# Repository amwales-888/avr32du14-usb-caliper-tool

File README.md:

# avr32du14-usb-caliper-tool
Tools that connects to caliper port to provide USB connectivity.

Q. What does it do?</BR>
A. You plug it in to your caliper, measure something and press the button, the value is sent to the USB Host as though it was typed by a keyboard.</BR>

The initial PCB run is being made base on the current kicad/avr32du14/production/avr32du14.zip
The enclosure was 3d printed in PLA using a 0.2mm nozzle. It is unlikely to print with 0.4 nozzles without additional work as the wall thicknesses are so thin.
Firmware has not be written but should be fairly trivial as it is simply a USB HID keyboard interface along with some additional code to obtain the values from the caliper.
This is very much a work in progress but I needed somewhere to stash the project.

<table>
  <tr>
    <td> </td>
    <td> </td>
  </tr>
  <tr>
    <td> </td>
    <td> </td>
  </tr>
  <tr>
    <td> </td>
    <td> </td>
  </tr>
  <tr>
    <td> </td>
  </tr>
</table>

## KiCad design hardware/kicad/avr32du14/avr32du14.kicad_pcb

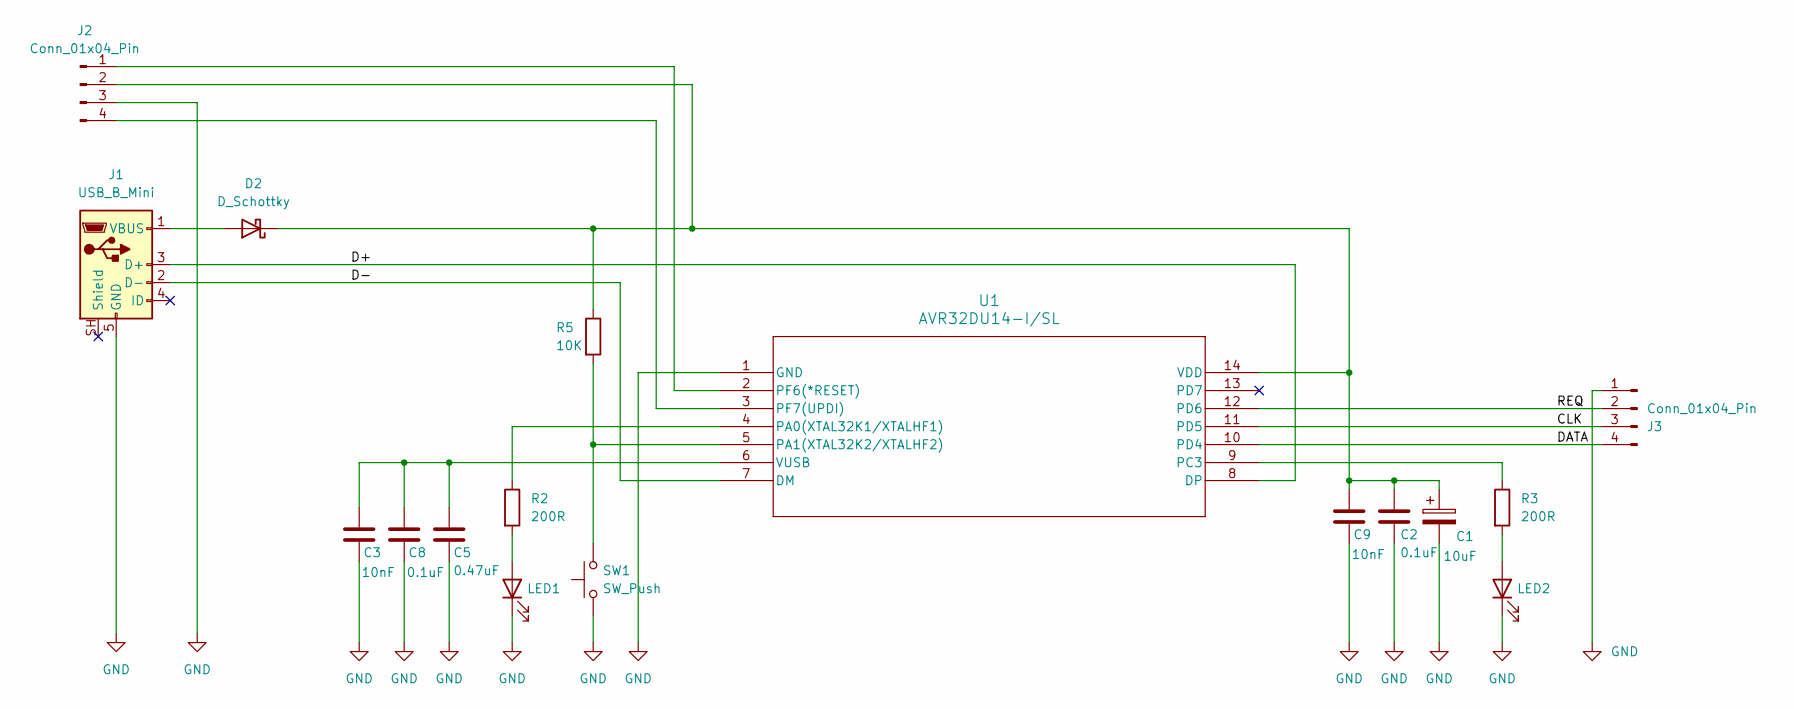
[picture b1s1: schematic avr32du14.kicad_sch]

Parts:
C1: 10uF; CP_EIA-3216-18_Kemet-A
C2, C8: 0.1uF; C_0603_1608Metric
C3, C9: 10nF; C_0603_1608Metric
C5: 0.47uF; C_0603_1608Metric
D2: D_Schottky; D_SOD-323_HandSoldering
J1: USB_B_Mini; USB_Mini-B_Wuerth_65100516121_Horizontal
J2, J3: Conn_01x04_Pin; PinHeader_1x04_P2.00mm_Vertical
LED1, LED2: LED; LED_0603_1608Metric_Pad1.05x0.95mm_HandSolder; MPN C7496820
R2, R3: 200R; R_0603_1608Metric; MPN C174076
R5: 10K; R_0603_1608Metric
SW1: SW_Push; SW_Tactile_SPST_NO_Straight_CK_PTS636Sx25SMTRLFS
U1: AVR32DU14-I/SL; SOIC14_SL_MCH-M

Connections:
/CLK: J3.3, U1.11 (PD5)
/D+: J1.3 (D+), U1.8 (DP)
/D-: J1.2 (D-), U1.7 (DM)
/DATA: J3.4, U1.10 (PD4)
/REQ: J3.2, U1.12 (PD6)
GND: C1.2, C2.2, C3.2, C5.2, C8.2, C9.2, J1.5 (GND), J2.3, J3.1, LED1.1 (K), LED2.1 (K), SW1.1, U1.1 (GND)
unnamed: D2.2 (A), J1.1 (VBUS)
unnamed: C1.1, C2.1, C9.1, D2.1 (K), J2.2, R5.1, U1.14 (VDD)
unnamed: J2.1, U1.2 (PF6(*RESET))
unnamed: J2.4, U1.3 (PF7(UPDI))
unnamed: LED1.2 (A), R2.2
unnamed: LED2.2 (A), R3.2
unnamed: R2.1, U1.4 (PA0(XTAL32K1/XTALHF1))
unnamed: R5.2, SW1.2, U1.5 (PA1(XTAL32K2/XTALHF2))
unnamed: R3.1, U1.9 (PC3)
unnamed: C3.1, C5.1, C8.1, U1.6 (VUSB)

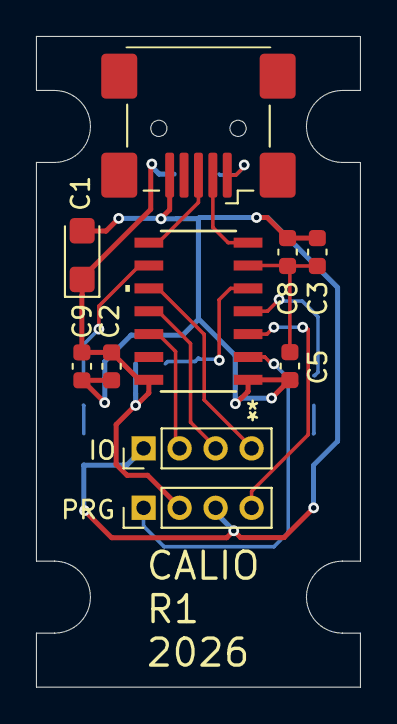
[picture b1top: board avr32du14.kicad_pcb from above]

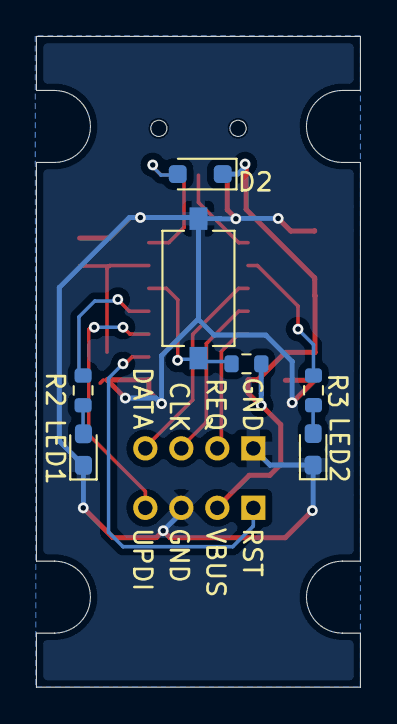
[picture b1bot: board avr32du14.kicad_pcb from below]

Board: 2 copper layers, 18.0 x 36.2 mm, 17 parts (7 on the bottom side), 16 nets.

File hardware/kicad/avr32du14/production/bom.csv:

Designator,Footprint,Quantity,Value,LCSC Part #
C1,CP_EIA-3216-18_Kemet-A,1,10uF,
"C2, C8",0603,2,0.1uF,
"C3, C9",0603,2,10nF,
C5,0603,1,0.47uF,
D2,D_SOD-323_HandSoldering,1,D_Schottky,
J1,USB_Mini-B_Wuerth_65100516121_Horizontal,1,USB_B_Mini,
"J2, J3",PinHeader_1x04_P2.00mm_Vertical,2,Conn_01x04_Pin,
"LED1, LED2",0603,2,LED,C7496820
"R2, R3",0603,2,200R,C174076
R5,0603,1,10K,
SW1,SW_Tactile_SPST_NO_Straight_CK_PTS636Sx25SMTRLFS,1,SW_Push,
U1,SOIC14_SL_MCH-M,1,AVR32DU14-I/SL,
